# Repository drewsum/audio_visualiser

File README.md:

# Audio Visualizer

## Hardware

A graphical EQ display, based on a dsPIC33AK256MPS105 digital signal controller.

### DSP Board:
* Distributes power to LED screens
* Digitizes RCA or speaker level audio signals
* Offsets AC audio signal to +1.6V reference for single-ended ADC conversions
* Adjustable gain or attenuation to fully utilize ADC range
* ~20kHz low-pass active filter for anti-aliasing
* USB Port (virtual COM) for debug and settings
* LED Panel Control

## Continuous integration

GitHub Actions checks every KiCad project under `hdw/` (`.github/workflows/hardware.yml`):

| Job | What it does |
|---|---|
| Repo hygiene | Fails on committed backups, lock files or caches, and on files not saved by KiCad 10.0. Checks that each project's schematic PDF (`<project>.pdf`) is committed and was re-plotted after the last schematic change. |
| ERC / DRC / libraries | Runs ERC, and DRC with schematic parity. Also checks that every symbol and footprint library resolves on a clean machine (project lib tables must use `${KIPRJMOD}`). 
| Visual diff | On every run, renders changed schematic pages and PCB layers against the previous commit or PR base (red = removed, green = added). The result is a single `visual-diff.html` artifact that opens directly in the browser; the run summary links to it. |

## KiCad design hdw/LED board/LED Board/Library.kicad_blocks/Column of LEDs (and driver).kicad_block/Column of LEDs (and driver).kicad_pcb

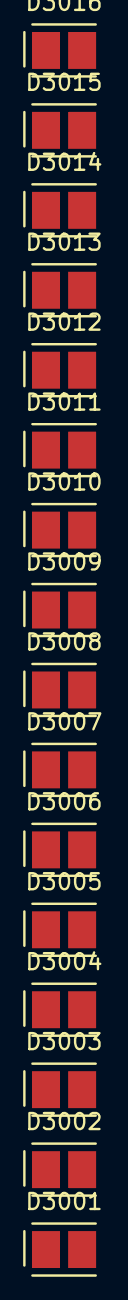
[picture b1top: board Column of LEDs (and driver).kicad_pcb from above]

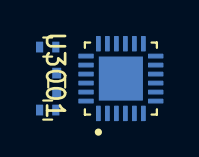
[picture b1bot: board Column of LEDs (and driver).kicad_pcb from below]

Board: 2 copper layers, 20 parts (4 on the bottom side), 21 nets, no tracks yet.

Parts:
C3001: 0.1uF; C_0402
D3001, D3002, D3003, D3004, D3005, D3006, D3007, D3008, D3009, D3010, D3011: GREEN; LED_LST676_AOS
D3012, D3013, D3014: YELLOW; LED_LST676_AOS
D3015, D3016: RED; LED_LST676_AOS
R3001: 2.52k; R_0402
R3002: 10k; R_0402
U3001: TLC59281RGER; QFN50P400X400X100-25N

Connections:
+3.3V: C3001.1, U3001.21 (VCC)
GND: C3001.2, R3001.2, R3002.2, U3001.22 (GND), U3001.25 (EP)
unnamed: D3001.1 (K), U3001.2 (OUT0)
unnamed: D3002.1 (K), U3001.3 (OUT1)
unnamed: D3003.1 (K), U3001.4 (OUT2)
unnamed: D3004.1 (K), U3001.5 (OUT3)
unnamed: D3005.1 (K), U3001.6 (OUT4)
unnamed: D3006.1 (K), U3001.7 (OUT5)
unnamed: D3007.1 (K), U3001.8 (OUT6)
unnamed: D3008.1 (K), U3001.9 (OUT7)
unnamed: D3009.1 (K), U3001.10 (OUT8)
unnamed: D3010.1 (K), U3001.11 (OUT9)
unnamed: D3011.1 (K), U3001.12 (OUT10)
unnamed: D3012.1 (K), U3001.13 (OUT11)
unnamed: D3013.1 (K), U3001.14 (OUT12)
unnamed: D3014.1 (K), U3001.15 (OUT13)
unnamed: D3015.1 (K), U3001.16 (OUT14)
unnamed: D3016.1 (K), U3001.17 (OUT15)
unnamed: R3001.1, U3001.20 (IREF)
SIN_0: R3002.1, U3001.23 (SIN)
VLED: D3001.2 (A), D3002.2 (A), D3003.2 (A), D3004.2 (A), D3005.2 (A), D3006.2 (A), D3007.2 (A), D3008.2 (A), D3009.2 (A), D3010.2 (A), D3011.2 (A), D3012.2 (A), D3013.2 (A), D3014.2 (A), D3015.2 (A), D3016.2 (A)
